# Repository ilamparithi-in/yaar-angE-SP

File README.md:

# yaar-angE-SP
Yaar ange? [Who's there?] - IoT attachment for primitive AC Calling Bell (Doorbell) 

\[README.md coming soon :P\]

<center>(IC missing :P and Antenna modification for better signal strength)

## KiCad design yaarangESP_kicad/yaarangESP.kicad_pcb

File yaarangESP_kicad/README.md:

Download the symbol and footprint of the HCPL3700 from here: https://www.snapeda.com/parts/HCPL-3700/Broadcom/view-part

Schematic made in KiCad 10.0

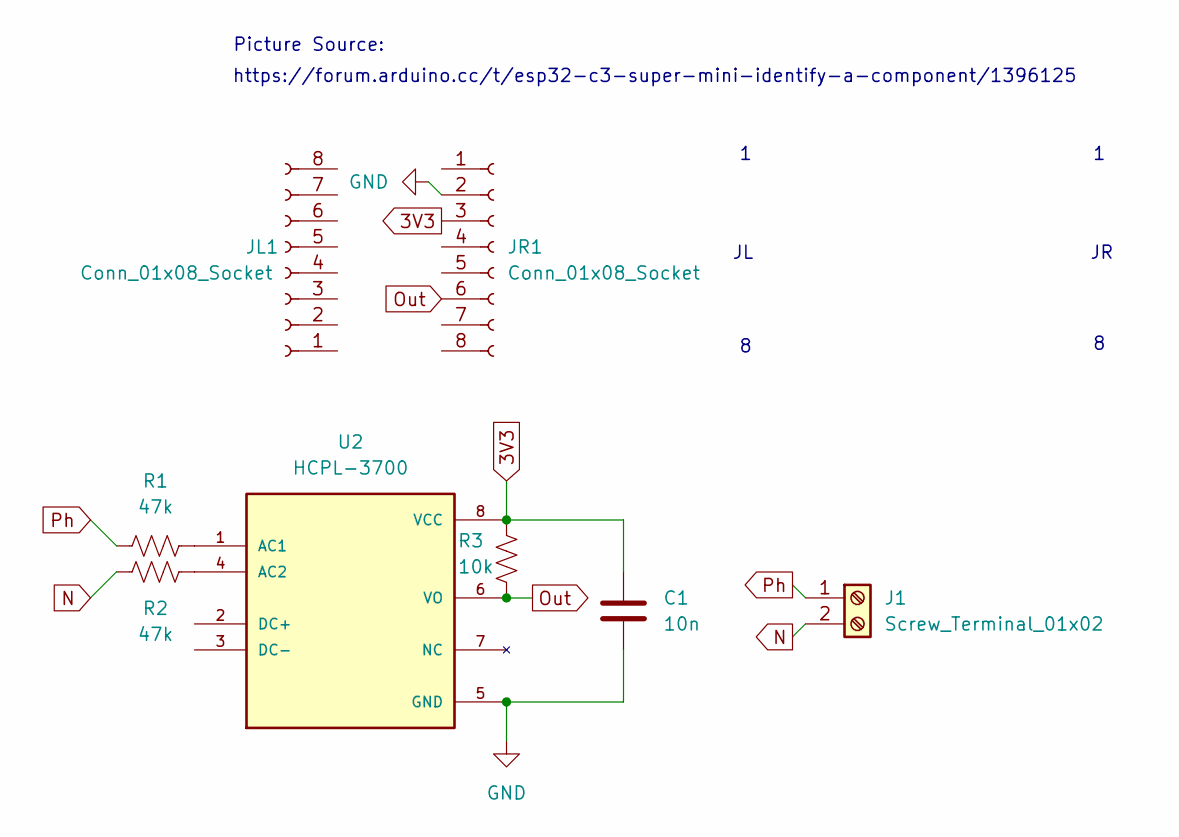
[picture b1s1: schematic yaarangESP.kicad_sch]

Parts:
C1: 10n; C_Disc_D5.0mm_W2.5mm_P5.00mm
J1: Screw_Terminal_01x02; TerminalBlock_Phoenix_MKDS-1,5-2-5.08_1x02_P5.08mm_Horizont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
JL1: Conn_01x08_Socket; PinSocket_1x08_P2.54mm_Vertical
JR1: Conn_01x08_Socket; PinSocket_1x08_P2.54mm_Vertical
R1, R2: 47k; R_Axial_DIN0207_L6.3mm_D2.5mm_P10.16mm_Horizontal
R3: 10k; R_Axial_DIN0207_L6.3mm_D2.5mm_P10.16mm_Horizontal
U2: HCPL-3700; DIP762W65P254L990H470Q8; PARTREV N/A

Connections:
3V3: C1.1, JR1.3, R3.2, U2.8 (VCC)
GND: C1.2, JR1.2, U2.5 (GND)
N: J1.2, R2.1
unnamed: R1.2, U2.1 (AC1)
unnamed: R2.2, U2.4 (AC2)
Out: JR1.6, R3.1, U2.6 (VO)
Ph: J1.1, R1.1

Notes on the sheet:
Picture Source:
https://forum.arduino.cc/t/esp32-c3-super-mini-identify-a-component/1396125

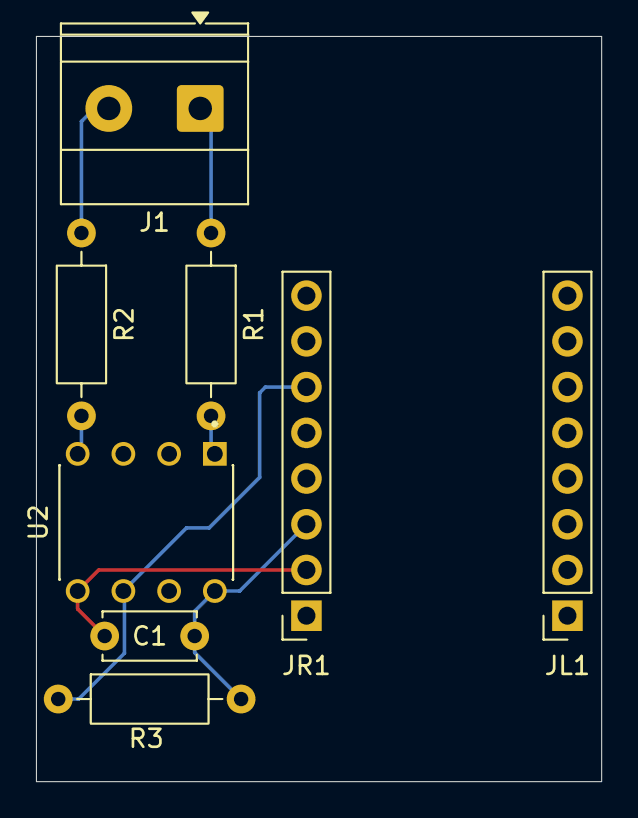
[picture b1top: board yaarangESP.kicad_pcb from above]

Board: 2 copper layers, 31.4 x 41.4 mm, 8 parts (0 on the bottom side), 7 nets.

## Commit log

2026-05-31 Upload verified code, images, and KiCad Project
2026-06-01 ESP32-C3 Supermini WiFi fix
